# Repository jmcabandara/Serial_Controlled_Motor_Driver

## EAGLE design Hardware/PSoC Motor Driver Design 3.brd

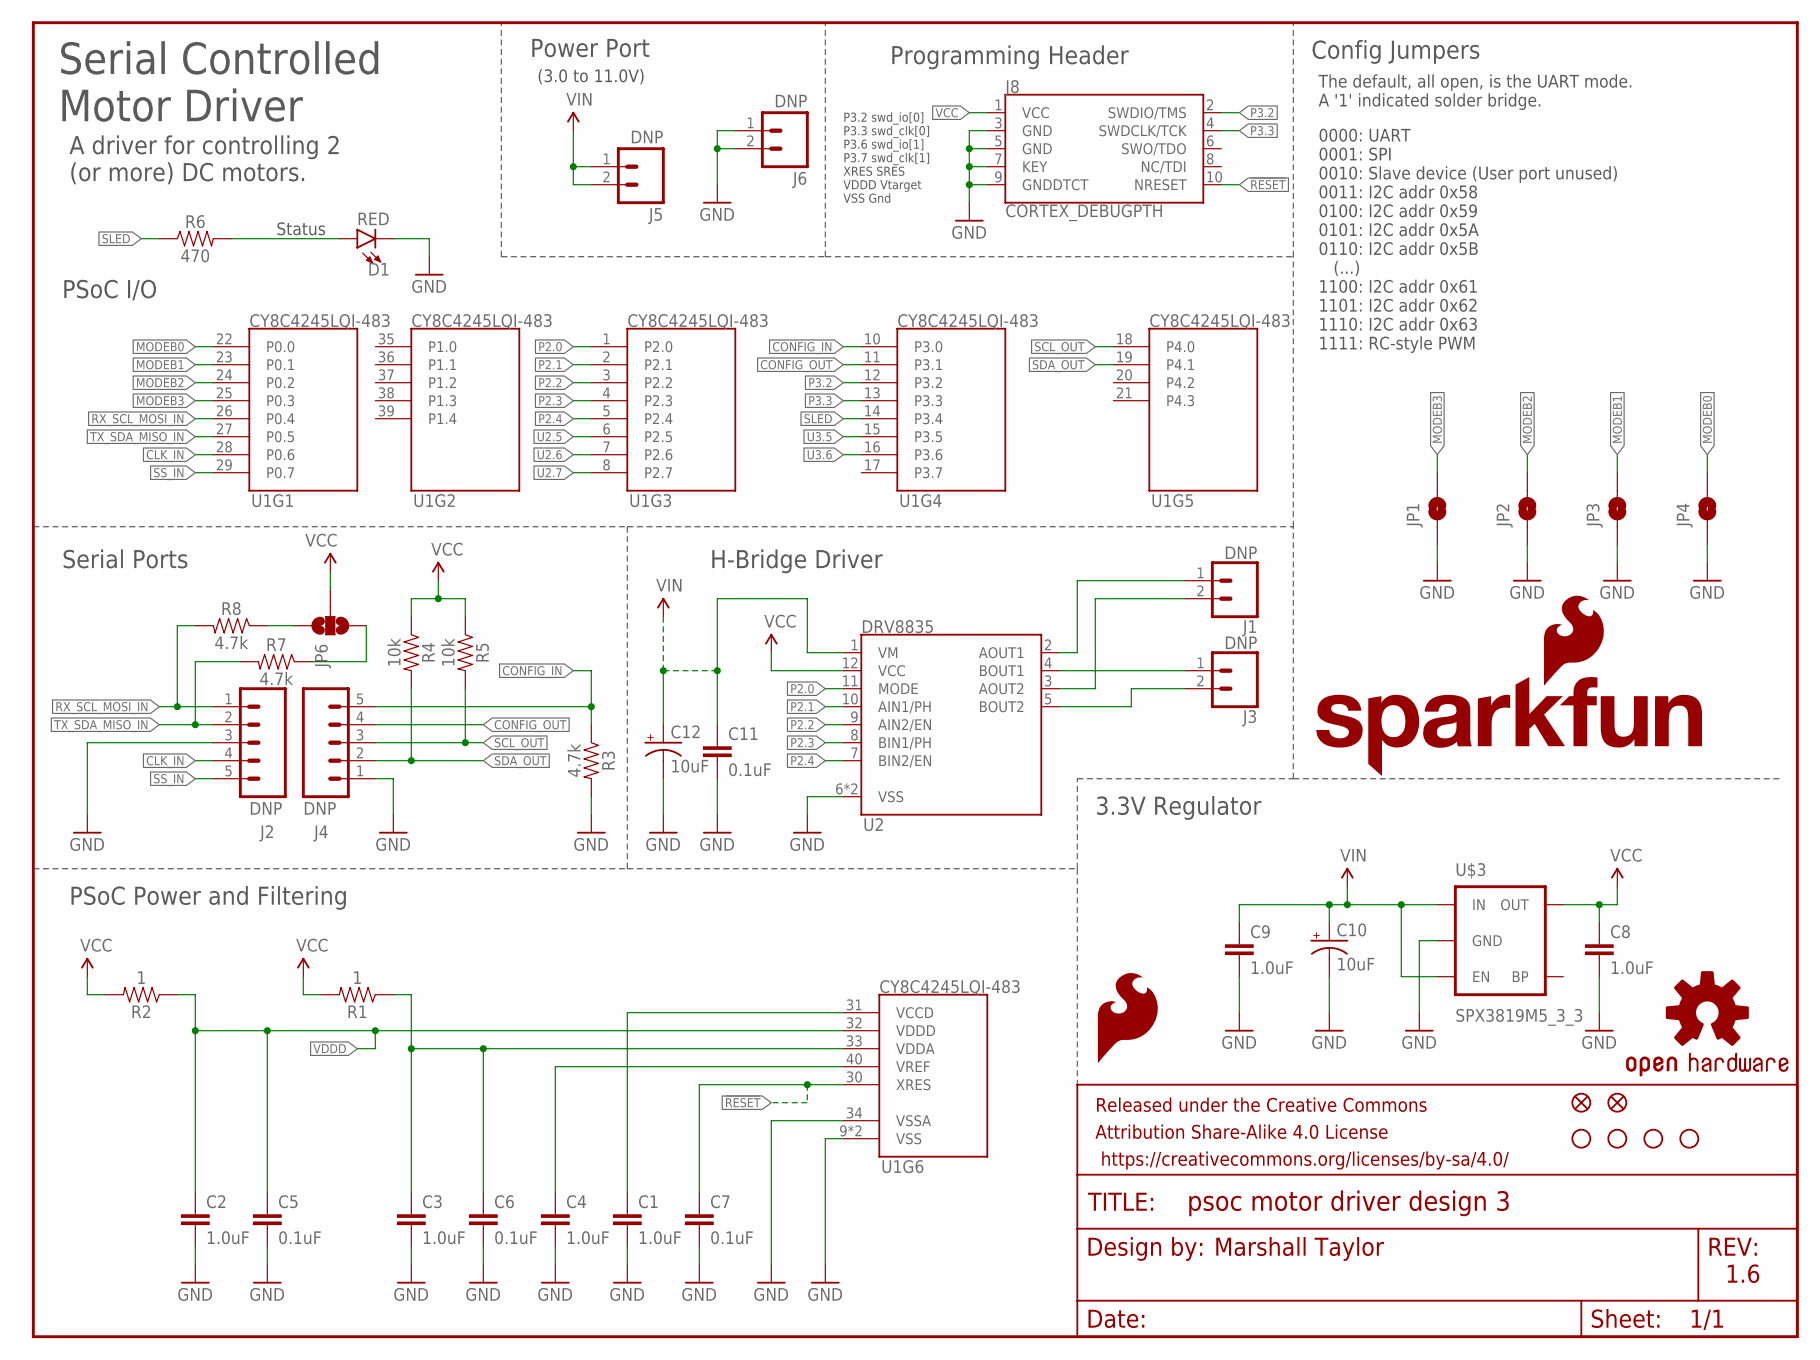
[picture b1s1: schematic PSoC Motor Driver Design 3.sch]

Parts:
C1, C2, C3, C4, C8, C9: 1.0uF; 0402
C5, C6, C7, C11: 0.1uF; 0402
C10, C12: 10uF; EIA3216
D1: RED; LED-0603
FD1, FD2: FIDUCIALUFIDUCIAL; MICRO-FIDUCIAL
FRAME1: FRAME-LETTER; CREATIVE_COMMONS
H1, H2, H3, H4: STAND-OFF
J1, J3: DNP; 1X02_NO_SILK
J2, J4: DNP; 1X05
J5, J6: DNP; 1X02@1
J8: CORTEX_DEBUGPTH; 2X5-PTH-1.27MM
JP1, JP2, JP3, JP4: JUMPER-PAD-2; PAD-JUMPER-2-NO_YES_SILK
JP6: JUMPER-PAD-3-NOYES_SILK; PAD-JUMPER-3-NO_YES_SILK
LOGO1: SFE_LOGO_FLAME.1_INCH; SFE_LOGO_FLAME_.1
LOGO2: OSHW-LOGOMINI; OSHW-LOGO-MINI
LOGO3: SFE_LOGO_NAME_FLAME.1_INCH; SFE_LOGO_NAME_FLAME_.1
R1, R2: 1; 0603
R3, R7, R8: 4.7k; 0603
R4, R5: 10k; 0603
R6: 470; 0603
U1: CY8C4245LQI-483; QFN-40
U2: DRV8835; WSON-12
U$3: SPX3819M5_3_3; SOT-23-5-VREG

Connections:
!RESET: C7.1, J8.10 (NRESET), U1.30 (XRES)
AOUT1: J1.1, U2.2 (AOUT1)
AOUT2: J1.2, U2.3 (AOUT2)
BOUT1: J3.1, U2.4 (BOUT1)
BOUT2: J3.2, U2.5 (BOUT2)
CLK_IN: J2.4, U1.28 (P0.6)
CONFIG_IN: J4.5, R3.1, U1.10 (P3.0)
CONFIG_OUT: J4.4, U1.11 (P3.1)
GND: C1.2, C2.2, C3.2, C4.2, C5.2, C6.2, C7.2, C8.2, C9.2, C10.-, C11.2, C12.-, D1.C, J2.3, J4.1, J6.1, J6.2, J8.3 (GND), J8.5 (GND), J8.7 (KEY), J8.9 (GNDDTCT), JP1.1, JP2.1, JP3.1, JP4.1, R3.2, U1.9 (VSS), U1.34 (VSSA), U1.EP (VSS), U2.6 (VSS), U2.PAD (VSS), U$3.2 (GND)
MODEB0: JP4.2, U1.22 (P0.0)
MODEB1: JP3.2, U1.23 (P0.1)
MODEB2: JP2.2, U1.24 (P0.2)
MODEB3: JP1.2, U1.25 (P0.3)
unnamed: C1.1, U1.31 (VCCD)
unnamed: C3.1, C6.1, R1.1, U1.33 (VDDA)
unnamed: C4.1, U1.40 (VREF)
unnamed: D1.A, R6.2
unnamed: JP6.1, R8.1
unnamed: JP6.3, R7.1
P2.0: U1.1 (P2.0), U2.11 (MODE)
P2.1: U1.2 (P2.1), U2.10 (AIN1/PH)
P2.2: U1.3 (P2.2), U2.9 (AIN2/EN)
P2.3: U1.4 (P2.3), U2.8 (BIN1/PH)
P2.4: U1.5 (P2.4), U2.7 (BIN2/EN)
P3.2: J8.2 (SWDIO/TMS), U1.12 (P3.2)
P3.3: J8.4 (SWDCLK/TCK), U1.13 (P3.3)
RX_SCL_MOSI_IN: J2.1, R8.2, U1.26 (P0.4)
SCL_OUT: J4.3, R5.2, U1.18 (P4.0)
SDA_OUT: J4.2, R4.2, U1.19 (P4.1)
SLED: R6.1, U1.14 (P3.4)
SS_IN: J2.5, U1.29 (P0.7)
TX_SDA_MISO_IN: J2.2, R7.2, U1.27 (P0.5)
U2.5: U1.6 (P2.5)
U2.6: U1.7 (P2.6)
U2.7: U1.8 (P2.7)
U3.5: U1.15 (P3.5)
U3.6: U1.16 (P3.6)
VCC: C8.1, J8.1 (VCC), JP6.2, R1.2, R2.2, R4.1, R5.1, U2.12 (VCC), U$3.5 (OUT)
VDDD: C2.1, C5.1, R2.1, U1.32 (VDDD)
VIN: C9.1, C10.+, C11.1, C12.+, J5.1, J5.2, U2.1 (VM), U$3.1 (IN), U$3.3 (EN)

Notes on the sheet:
PSoC Power and Filtering
Serial Controlled Motor Driver
Config Jumpers
Marshall Taylor
PSoC I/O
3.3V Regulator
1.6
P3.2 swd_io[0] P3.3 swd_clk[0] P3.6 swd_io[1] P3.7 swd_clk[1] XRES SRES VDDD Vtarget VSS Gnd
Serial Ports
Power Port
Programming Header
H-Bridge Driver
A driver for controlling 2 (or more) DC motors.
0000: UART 0001: SPI 0010: Slave device (User port unused) 0011: I2C addr 0x58 0100: I2C addr 0x59 0101: I2C addr 0x5A 0110: I2C addr 0x5B (...) 1100: I2C addr 0x61 1101: I2C addr 0x62 1110: I2C addr 0x63 1111: RC-style PWM
The default, all open, is the UART mode. A '1' indicated solder bridge.
Status
(3.0 to 11.0V)

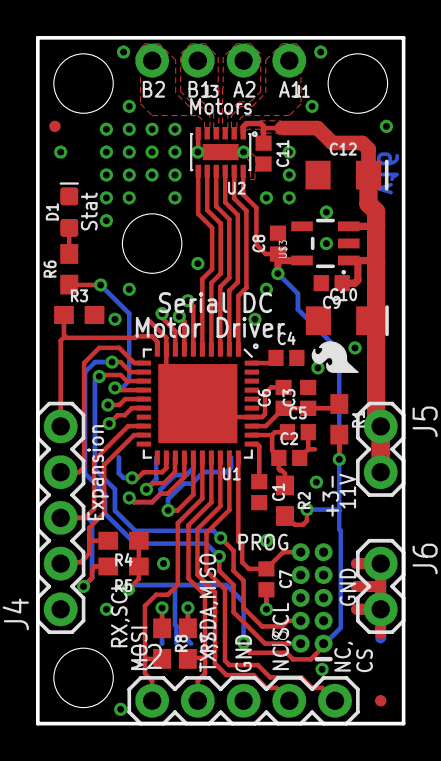
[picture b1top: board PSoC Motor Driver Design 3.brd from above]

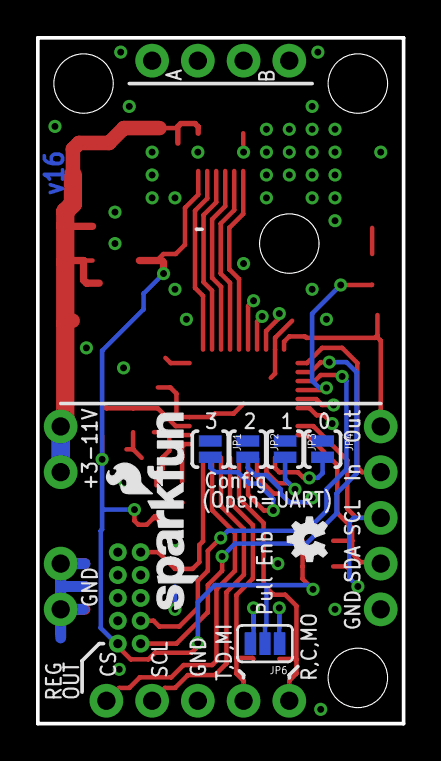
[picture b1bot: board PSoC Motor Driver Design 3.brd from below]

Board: 2 copper layers, 20.3 x 38.1 mm, 46 parts (7 on the bottom side), 35 nets.

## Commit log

2016-04-26 Introducing serial psoc project and fixing github issues
2016-04-26 Updated schematic docu
2016-06-28 First proto tested and firmware bring-up code has been written to validate capibilities of the psoc. Release firmware has been started and is partially functional. Hardware has undergone major revisi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
2016-06-29 Fixed schematic naming, touched up other changes, tested 2nd serial port, reved board number
2016-06-29 added .gitignore file to try and remove non-essential psoc build files
2016-06-30 Prepping for QC, tuning gitignores
2016-06-30 trying new gitignore location
2016-06-30 testing new gitignore
2016-06-30 saving last real FW change
2016-06-30 Ready to rebranch. Now, PSoC projects will only track the minimum files required to rebuild the projects.
2016-06-30 Deleted the board files to prevent confusion -- do not use this branch

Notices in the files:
parts and their libraries:
SparkFun-Capacitors: Licensing: Creative Commons ShareAlike 4.0 International - https://creativecommons.org/licenses/by-sa/4.0
SparkFun-Aesthetics: Released under the Creative Commons Attribution Share-Alike 4.0 License
SparkFun-Aesthetics: https://creativecommons.org/licenses/by-sa/4.0
